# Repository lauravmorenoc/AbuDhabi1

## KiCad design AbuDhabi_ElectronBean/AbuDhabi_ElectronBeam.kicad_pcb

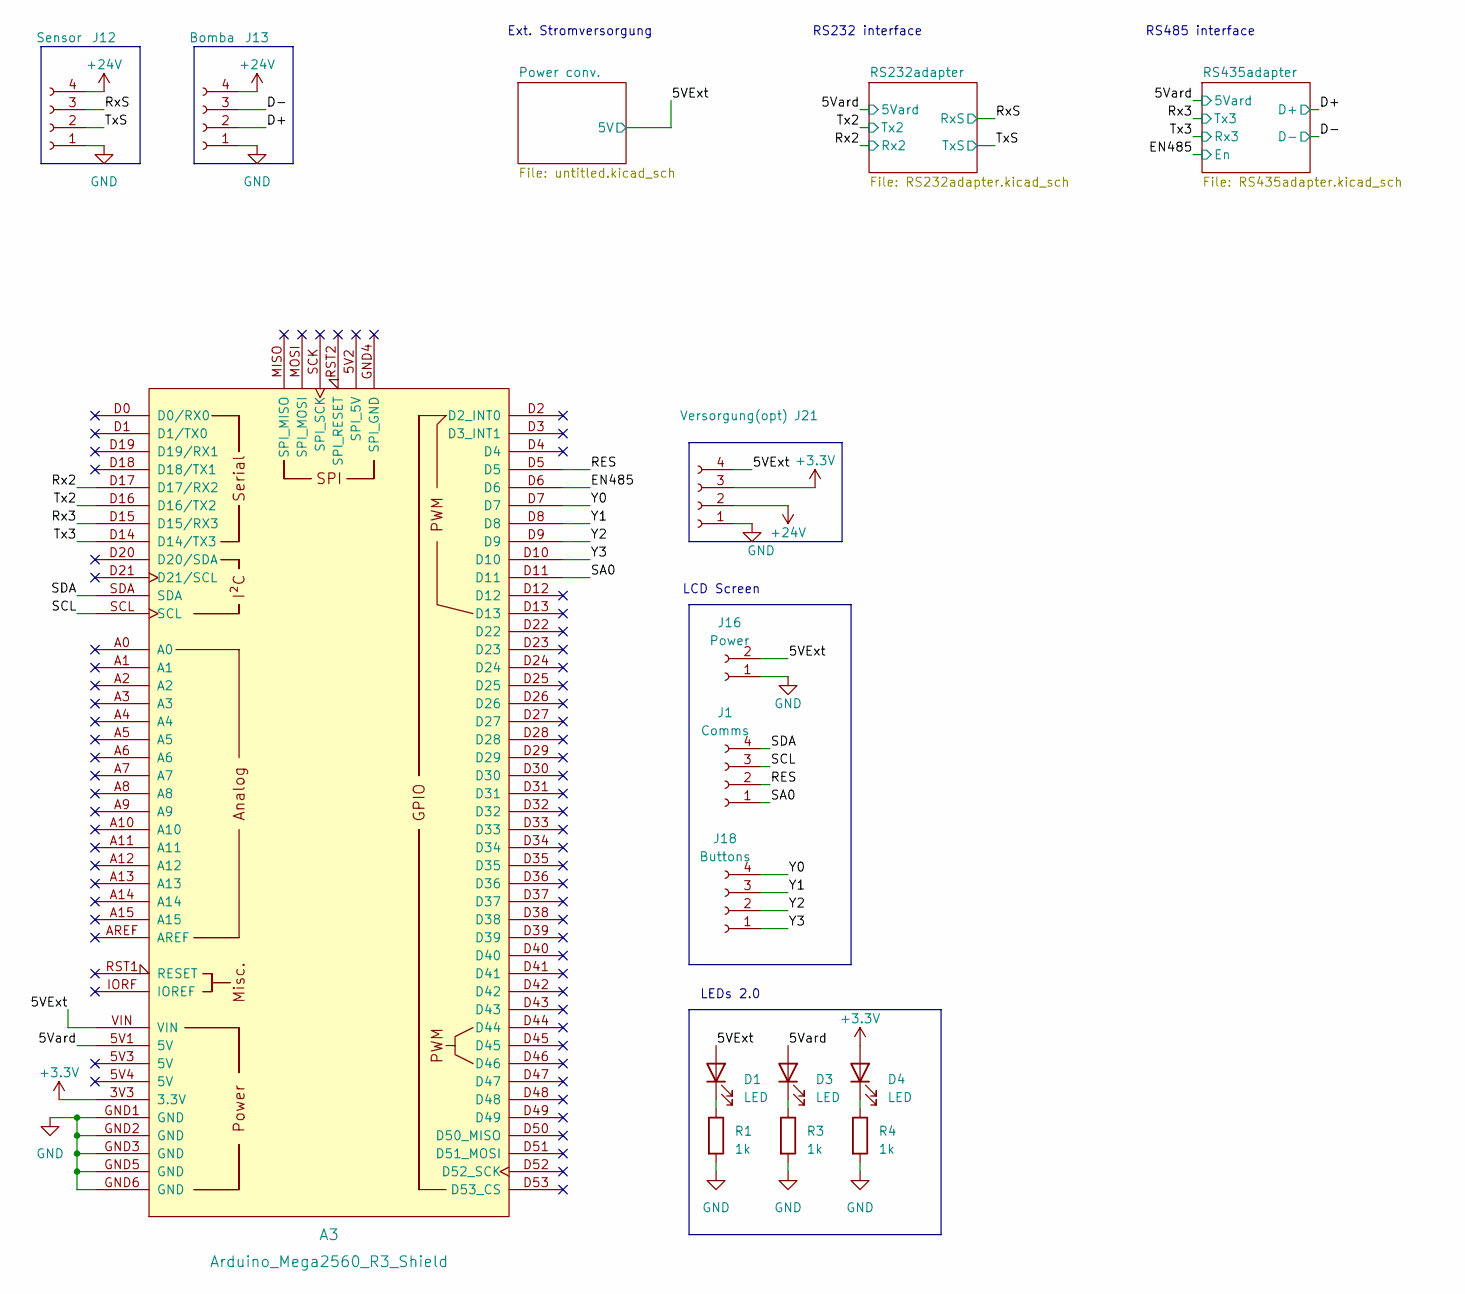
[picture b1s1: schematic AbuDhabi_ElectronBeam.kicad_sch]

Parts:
A3: Arduino_Mega2560_R3_Shield
D1, D3, D4: LED; LED_0603_1608Metric_Pad1.05x0.95mm_HandSolder
J1: Comms; PinSocket_1x04_P2.54mm_Vertical
J12: Sensor; JST_EH_B4B-EH-A_1x04_P2.50mm_Vertical
J13: Bomba; JST_EH_B4B-EH-A_1x04_P2.50mm_Vertical
J16: Power; PinSocket_1x02_P2.54mm_Vertical
J18: Buttons; PinSocket_1x04_P2.54mm_Vertical
J21: Versorgung(opt); JST_EH_B4B-EH-A_1x04_P2.50mm_Vertical
R1, R3, R4: 1k; R_0603_1608Metric_Pad0.98x0.95mm_HandSolder

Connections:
+3.3V: A3.3V3 (3.3V), D4.2 (A), J21.3
/5Vard: A3.5V1 (5V), D3.2 (A); also elsewhere on the board
/D+: J13.2; also elsewhere on the board
/D-: J13.3; also elsewhere on the board
/EN485: A3.D6; also elsewhere on the board
/RES: A3.D5, J1.2
/Rx2: A3.D17 (D17/RX2); also elsewhere on the board
/Rx3: A3.D15 (D15/RX3); also elsewhere on the board
/RxS: J12.3; also elsewhere on the board
/SA0: A3.D11, J1.1
/SCL: A3.SCL, J1.3
/SDA: A3.SDA, J1.4
/Tx2: A3.D16 (D16/TX2); also elsewhere on the board
/Tx3: A3.D14 (D14/TX3); also elsewhere on the board
/TxS: J12.2; also elsewhere on the board
/Y0: A3.D7, J18.4
/Y1: A3.D8, J18.3
/Y2: A3.D9, J18.2
/Y3: A3.D10, J18.1
GND: A3.GND1 (GND), A3.GND2 (GND), A3.GND3 (GND), A3.GND5 (GND), A3.GND6 (GND), J12.1, J13.1, J16.1, J21.1, R1.2, R3.2, R4.2; also elsewhere on the board
unnamed: D1.1 (K), R1.1
unnamed: D3.1 (K), R3.1
unnamed: D4.1 (K), R4.1

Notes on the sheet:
LCD Screen
Ext. Stromversorgung
RS485 interface
RS232 interface
LEDs 2.0

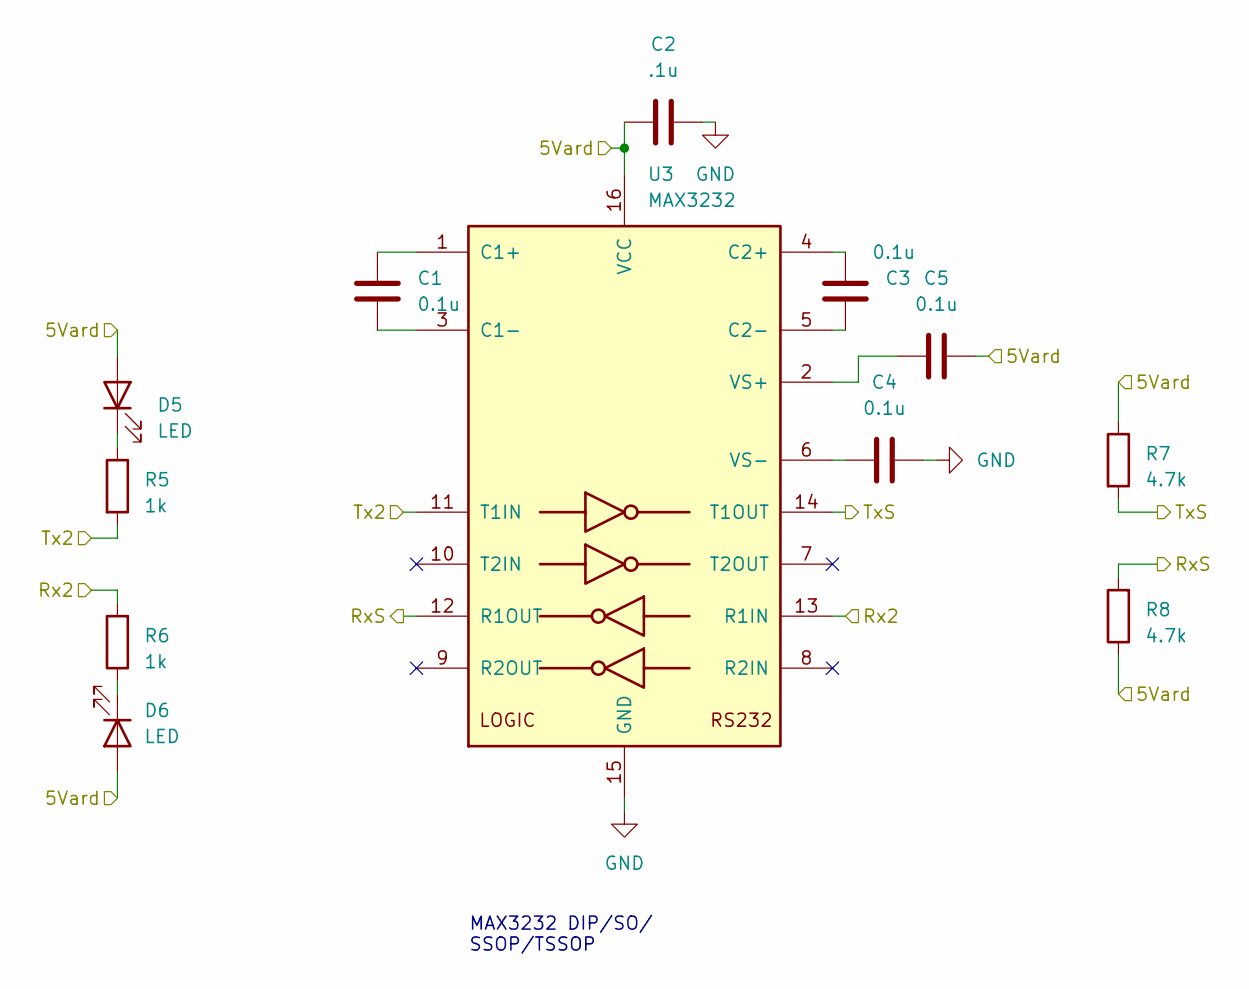
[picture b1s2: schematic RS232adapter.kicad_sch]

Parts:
C1, C3, C4, C5: 0.1u; C_0603_1608Metric
C2: .1u; C_0603_1608Metric
D5: LED; LED_0603_1608Metric
D6: LED; LED_0603_1608Metric_Pad1.05x0.95mm_HandSolder
R5, R6: 1k; R_0603_1608Metric
R7, R8: 4.7k; R_0603_1608Metric
U3: MAX3232; SOIC-16_3.9x9.9mm_P1.27mm

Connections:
/5Vard: C2.1, C5.2, D5.2 (A), D6.2 (A), R7.1, R8.1, U3.16 (VCC); also elsewhere on the board
/Rx2: R6.2, U3.13 (R1IN); also elsewhere on the board
/RxS: R8.2, U3.12 (R1OUT); also elsewhere on the board
/Tx2: R5.2, U3.11 (T1IN); also elsewhere on the board
/TxS: R7.2, U3.14 (T1OUT); also elsewhere on the board
GND: C2.2, C4.2, U3.15 (GND); also elsewhere on the board
unnamed: D5.1 (K), R5.1
unnamed: D6.1 (K), R6.1
unnamed: C1.1, U3.1 (C1+)
unnamed: C1.2, U3.3 (C1-)
unnamed: C3.1, U3.4 (C2+)
unnamed: C3.2, U3.5 (C2-)
unnamed: C5.1, U3.2 (VS+)
unnamed: C4.1, U3.6 (VS-)

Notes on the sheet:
MAX3232 DIP/SO/ SSOP/TSSOP

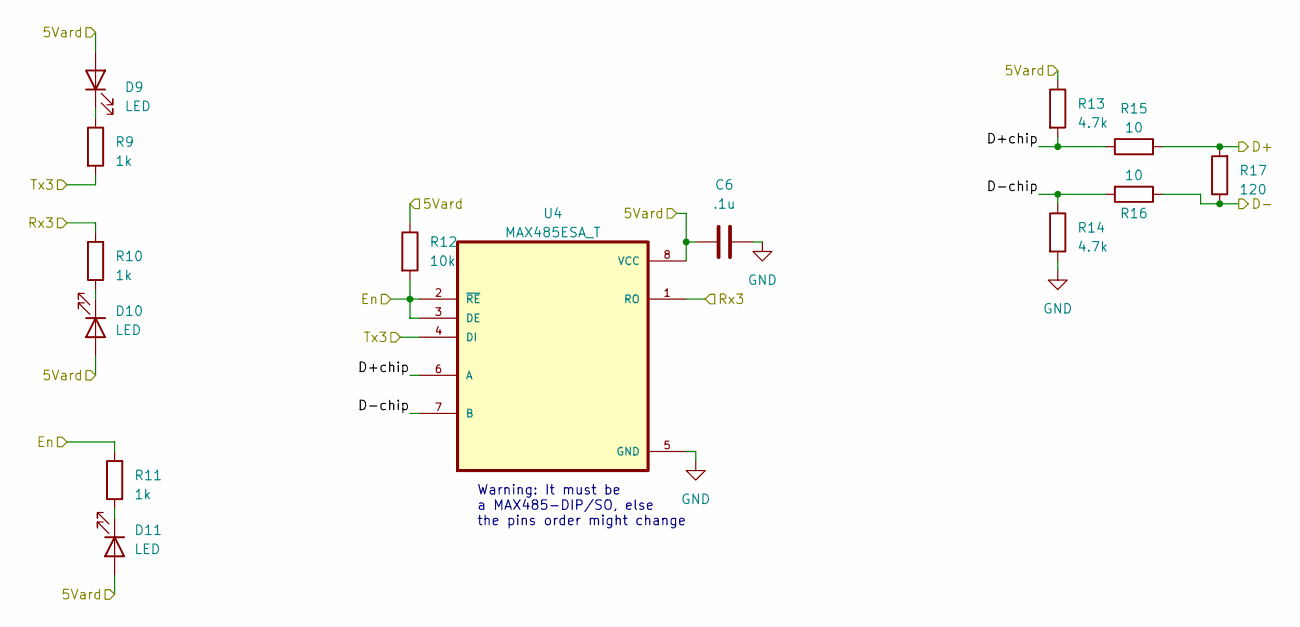
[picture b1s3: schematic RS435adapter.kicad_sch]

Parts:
C6: .1u; C_0603_1608Metric
D9, D10, D11: LED; LED_0603_1608Metric
R9, R10, R11: 1k; R_0603_1608Metric
R12: 10k; R_0603_1608Metric
R13, R14: 4.7k; R_0603_1608Metric
R15, R16: 10; R_0603_1608Metric
R17: 120; R_0603_1608Metric
U4: MAX485ESA_T; SOIC127P600X175-8N

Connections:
/5Vard: C6.1, D9.2 (A), D10.2 (A), D11.2 (A), R12.1, R13.1, U4.8 (VCC); also elsewhere on the board
/D+: R15.2, R17.2; also elsewhere on the board
/D-: R16.1, R17.1; also elsewhere on the board
/EN485: R11.2, R12.2, U4.2 (~RE), U4.3 (DE); also elsewhere on the board
/RS435adapter/D+chip: R13.2, R15.1, U4.6 (A)
/RS435adapter/D-chip: R14.1, R16.2, U4.7 (B)
/Rx3: R9.2, U4.4 (DI); also elsewhere on the board
/Tx3: R10.2, U4.1 (RO); also elsewhere on the board
GND: C6.2, R14.2, U4.5 (GND); also elsewhere on the board
unnamed: D9.1 (K), R9.1
unnamed: D10.1 (K), R10.1
unnamed: D11.1 (K), R11.1

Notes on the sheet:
Warning: It must be a MAX485-DIP/SO, else the pins order might change

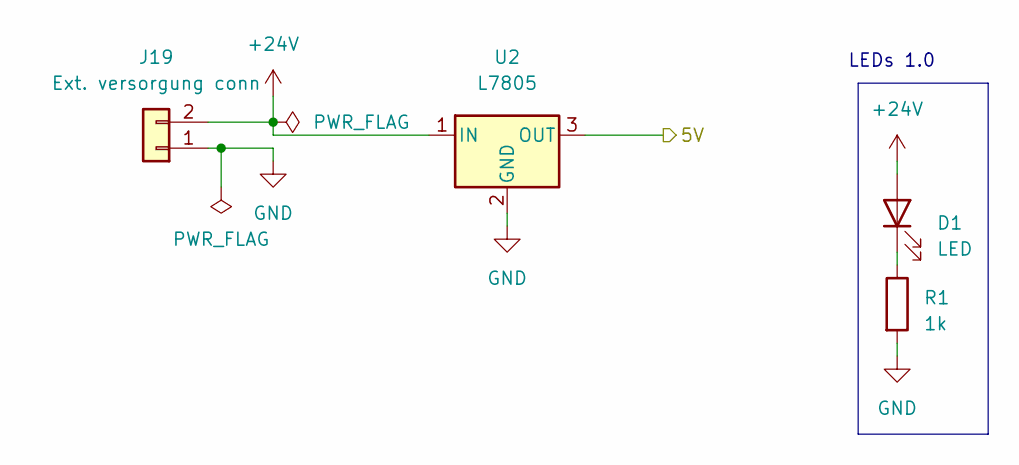
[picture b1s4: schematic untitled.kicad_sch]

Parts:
D1: LED; LED_0603_1608Metric_Pad1.05x0.95mm_HandSolder
J19: Ext. versorgung conn; JST_EH_B2B-EH-A_1x02_P2.50mm_Vertical
R1: 1k; R_0603_1608Metric
U2: L7805; TO-220-3_Vertical

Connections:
GND: J19.1, R1.2, U2.2 (GND); also elsewhere on the board
unnamed: D1.1 (K), R1.1

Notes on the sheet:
LEDs 1.0

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
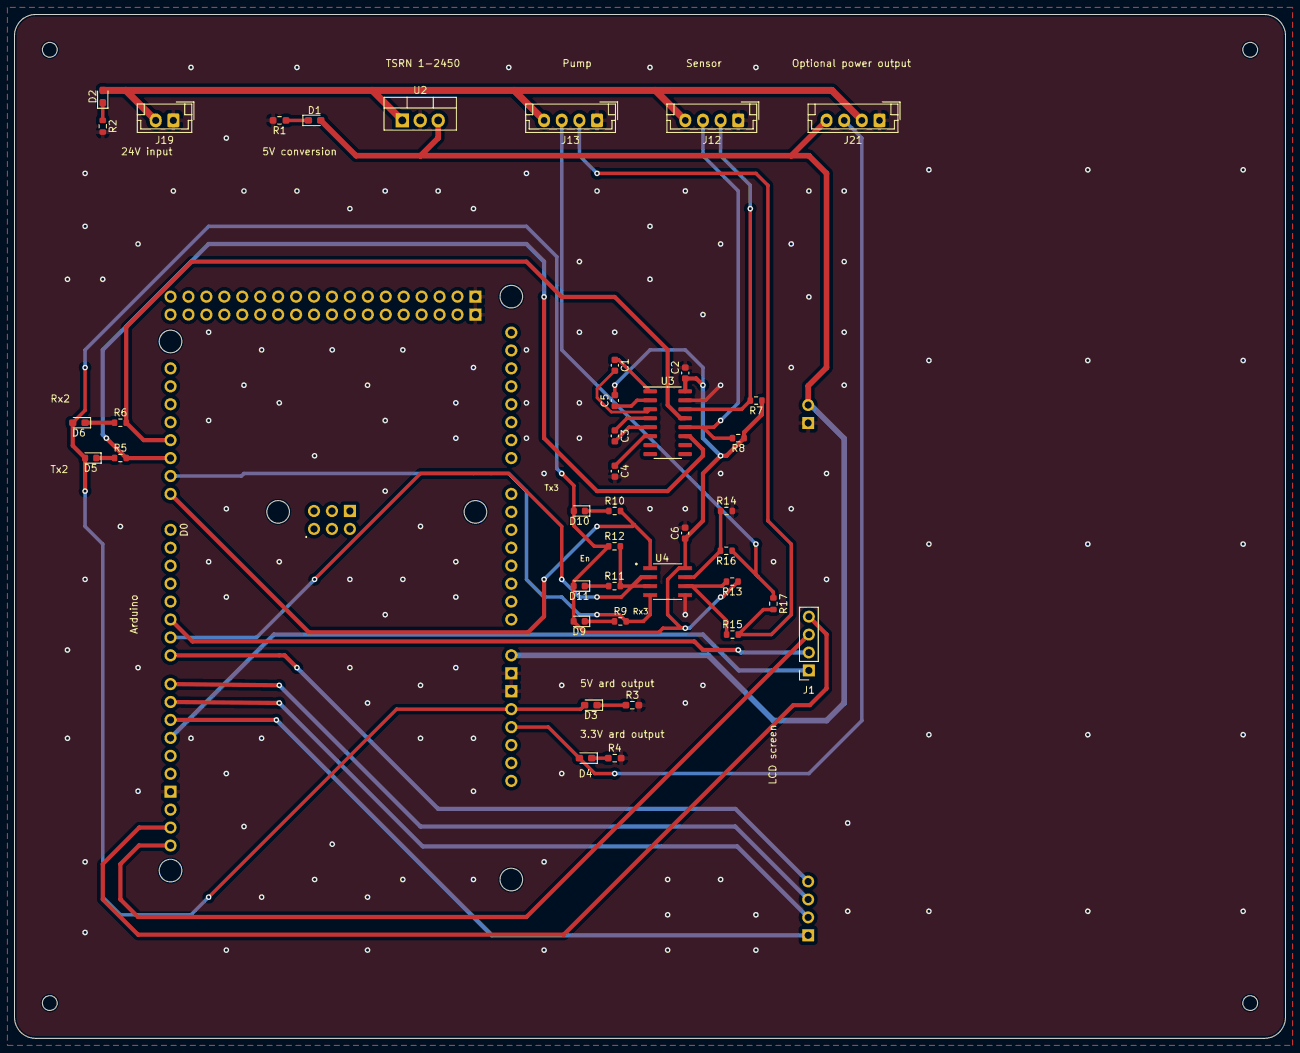
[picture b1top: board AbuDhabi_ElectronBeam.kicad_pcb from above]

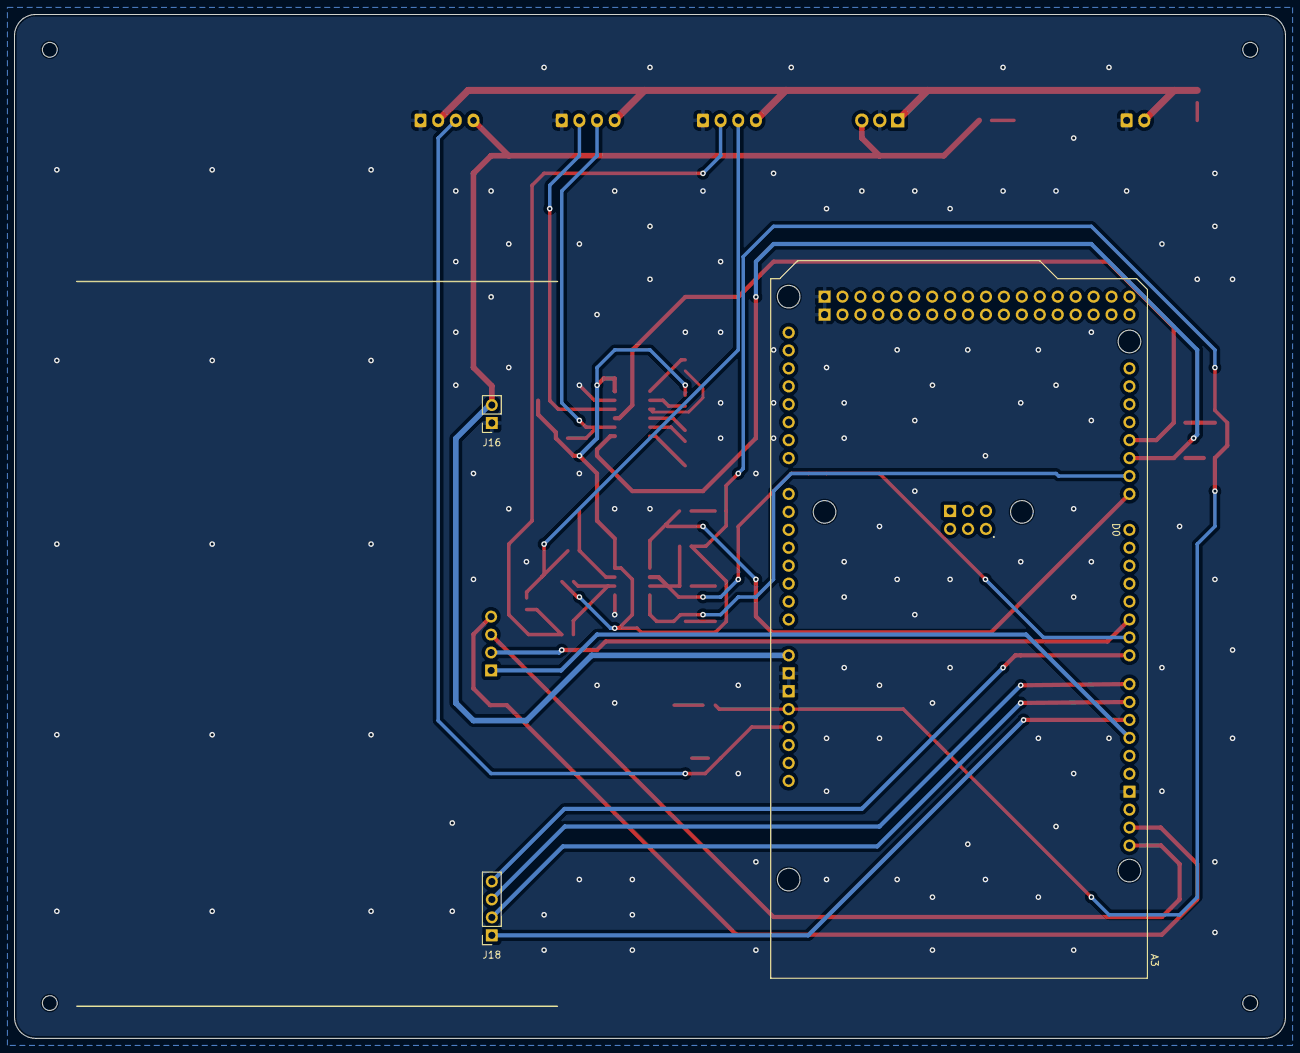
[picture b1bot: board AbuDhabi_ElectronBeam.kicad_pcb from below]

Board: 2 copper layers, 180.0 x 145.0 mm, 43 parts (2 on the bottom side), 39 nets.

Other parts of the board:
D2: LED; LED_0603_1608Metric_Pad1.05x0.95mm_HandSolder
R2: 1k; R_0603_1608Metric

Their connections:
GND: R2.2; also elsewhere on the board
unnamed: D2.1 (K), R2.1

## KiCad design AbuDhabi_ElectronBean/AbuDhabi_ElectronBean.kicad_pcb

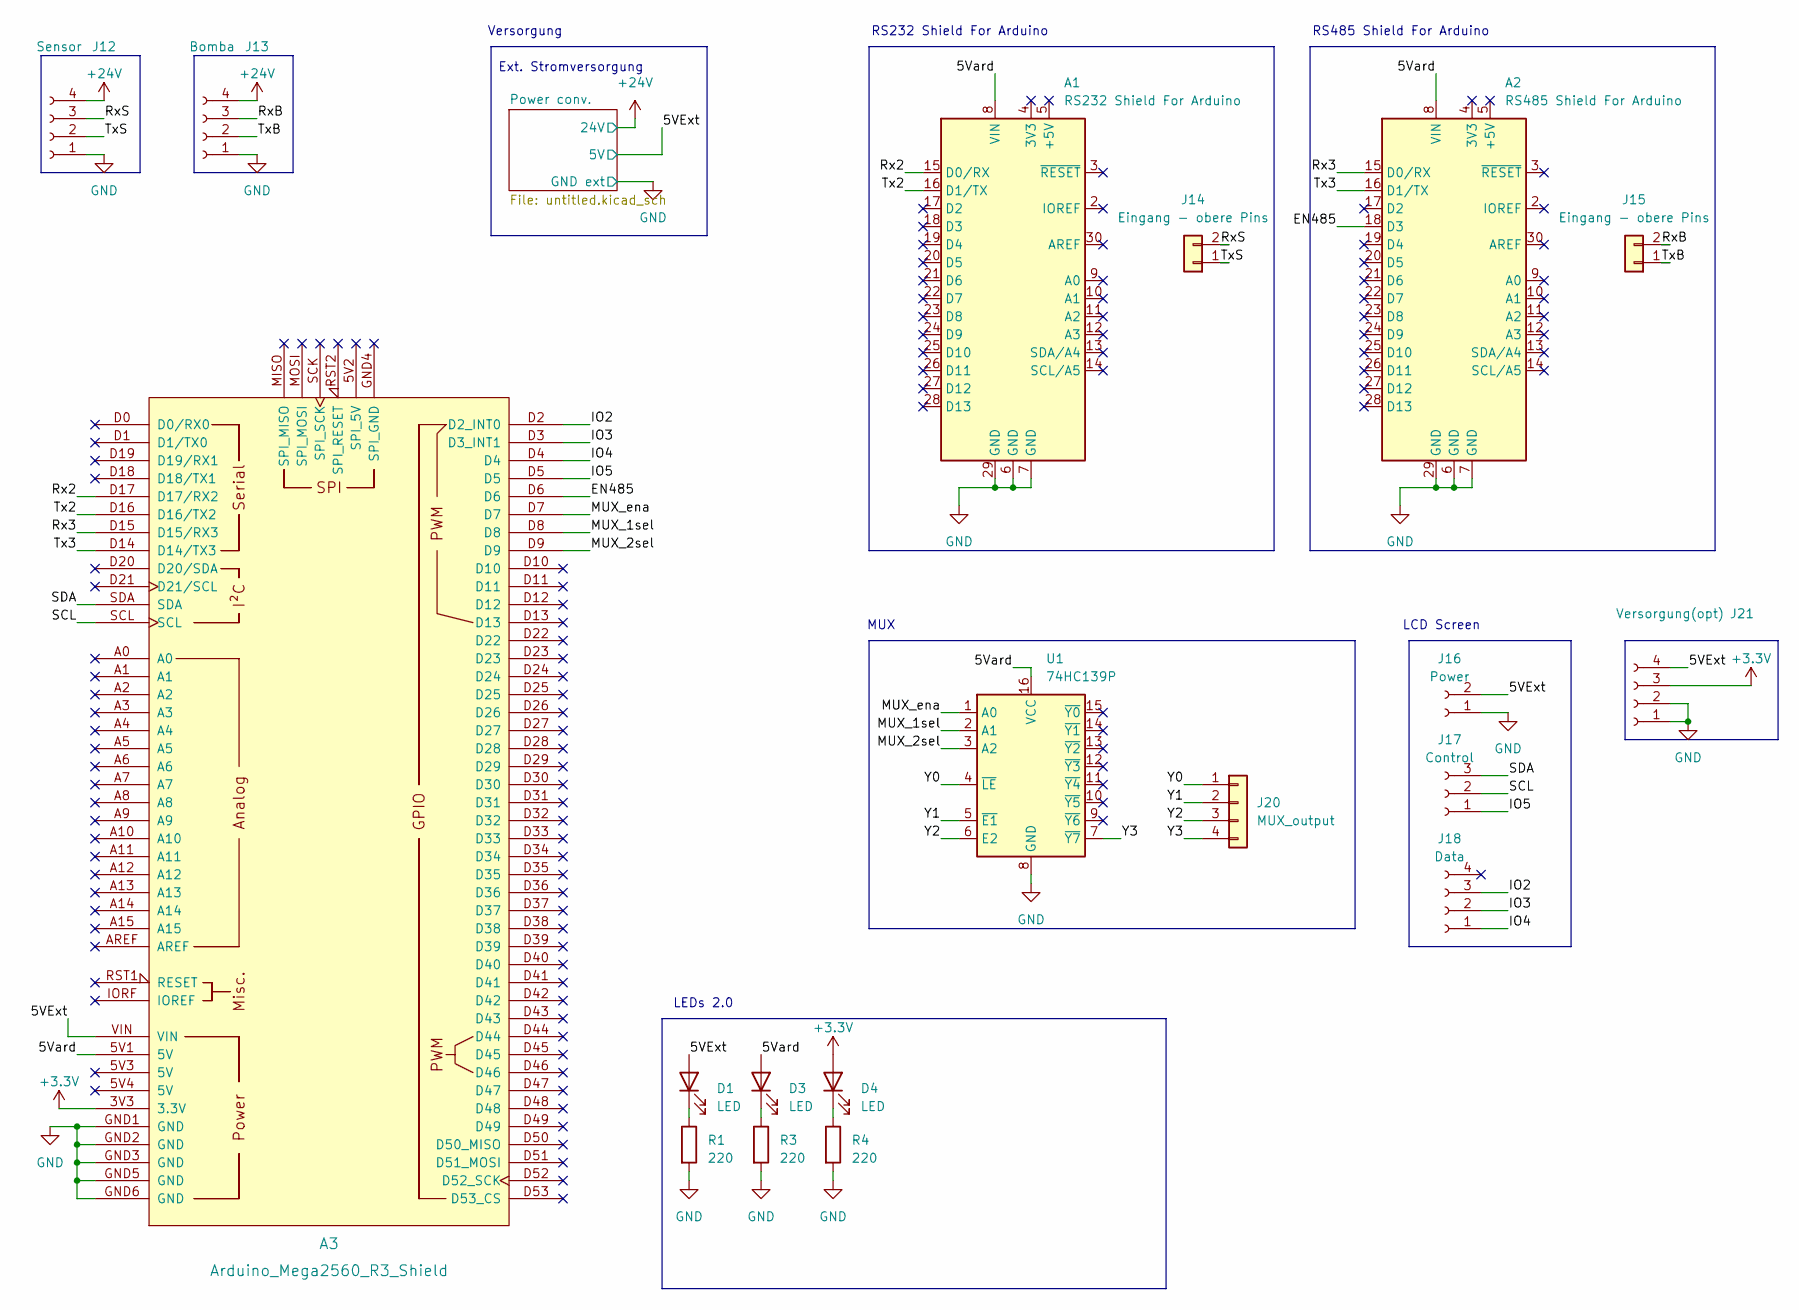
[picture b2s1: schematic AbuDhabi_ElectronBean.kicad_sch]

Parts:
A1: RS232 Shield For Arduino; Arduino_UNO_R2
A2: RS485 Shield For Arduino; Arduino_UNO_R2
A3: Arduino_Mega2560_R3_Shield
D1, D3, D4: LED; LED_0603_1608Metric_Pad1.05x0.95mm_HandSolder
J12: Sensor; JST_EH_B4B-EH-A_1x04_P2.50mm_Vertical
J13: Bomba; JST_EH_B4B-EH-A_1x04_P2.50mm_Vertical
J14, J15: Eingang - obere Pins; JST_EH_B2B-EH-A_1x02_P2.50mm_Vertical
J16: Power; PinSocket_1x02_P2.54mm_Vertical
J17: Control; PinSocket_1x03_P2.54mm_Vertical
J18: Data; PinSocket_1x04_P2.54mm_Vertical
J20: MUX_output; JST_EH_B4B-EH-A_1x04_P2.50mm_Vertical
J21: Versorgung(opt); JST_EH_B4B-EH-A_1x04_P2.50mm_Vertical
R1, R3, R4: 220; R_0805_2012Metric_Pad1.20x1.40mm_HandSolder
U1: 74HC139P; DIP-16_W7.62mm

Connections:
+3.3V: A3.3V3 (3.3V), D4.2 (A), J21.3
/5Vard: A1.8 (VIN), A2.8 (VIN), A3.5V1 (5V), D3.2 (A), U1.16 (VCC)
/EN485: A2.18 (D3), A3.D6
/IO2: A3.D2 (D2_INT0), J18.3
/IO3: A3.D3 (D3_INT1), J18.2
/IO4: A3.D4, J18.1
/IO5: A3.D5, J17.1
/MUX_1sel: A3.D8, U1.2 (A1)
/MUX_2sel: A3.D9, U1.3 (A2)
/MUX_ena: A3.D7, U1.1 (A0)
/Rx2: A1.15 (D0/RX), A3.D17 (D17/RX2)
/Rx3: A2.15 (D0/RX), A3.D15 (D15/RX3)
/RxB: J13.3, J15.2
/RxS: J12.3, J14.2
/SCL: A3.SCL, J17.2
/SDA: A3.SDA, J17.3
/Tx2: A1.16 (D1/TX), A3.D16 (D16/TX2)
/Tx3: A2.16 (D1/TX), A3.D14 (D14/TX3)
/TxB: J13.2, J15.1
/TxS: J12.2, J14.1
/Y0: J20.1, U1.4 (~LE)
/Y1: J20.2, U1.5 (~E1)
/Y2: J20.3, U1.6 (E2)
/Y3: J20.4, U1.7 (~Y7)
GND: A1.6 (GND), A1.7 (GND), A1.29 (GND), A2.6 (GND), A2.7 (GND), A2.29 (GND), A3.GND1 (GND), A3.GND2 (GND), A3.GND3 (GND), A3.GND5 (GND), A3.GND6 (GND), J12.1, J13.1, J16.1, J21.1, J21.2, R1.2, R3.2, R4.2, U1.8 (GND); also elsewhere on the board
unnamed: D1.1 (K), R1.1
unnamed: D3.1 (K), R3.1
unnamed: D4.1 (K), R4.1

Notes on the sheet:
RS232 Shield For Arduino
Versorgung
LCD Screen
Ext. Stromversorgung
RS485 Shield For Arduino
MUX
LEDs 2.0

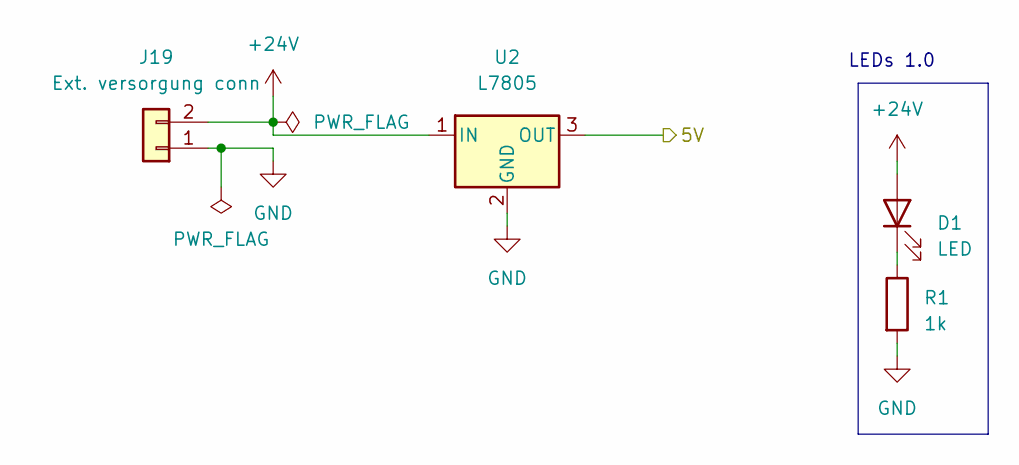
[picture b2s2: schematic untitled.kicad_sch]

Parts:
D1: LED; LED_0603_1608Metric_Pad1.05x0.95mm_HandSolder
J19: Ext. versorgung conn; JST_EH_B2B-EH-A_1x02_P2.50mm_Vertical
R1: 1k; R_0603_1608Metric
U2: L7805; TO-220-3_Vertical

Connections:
GND: J19.1, R1.2, U2.2 (GND); also elsewhere on the board
unnamed: D1.1 (K), R1.1

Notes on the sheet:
LEDs 1.0

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
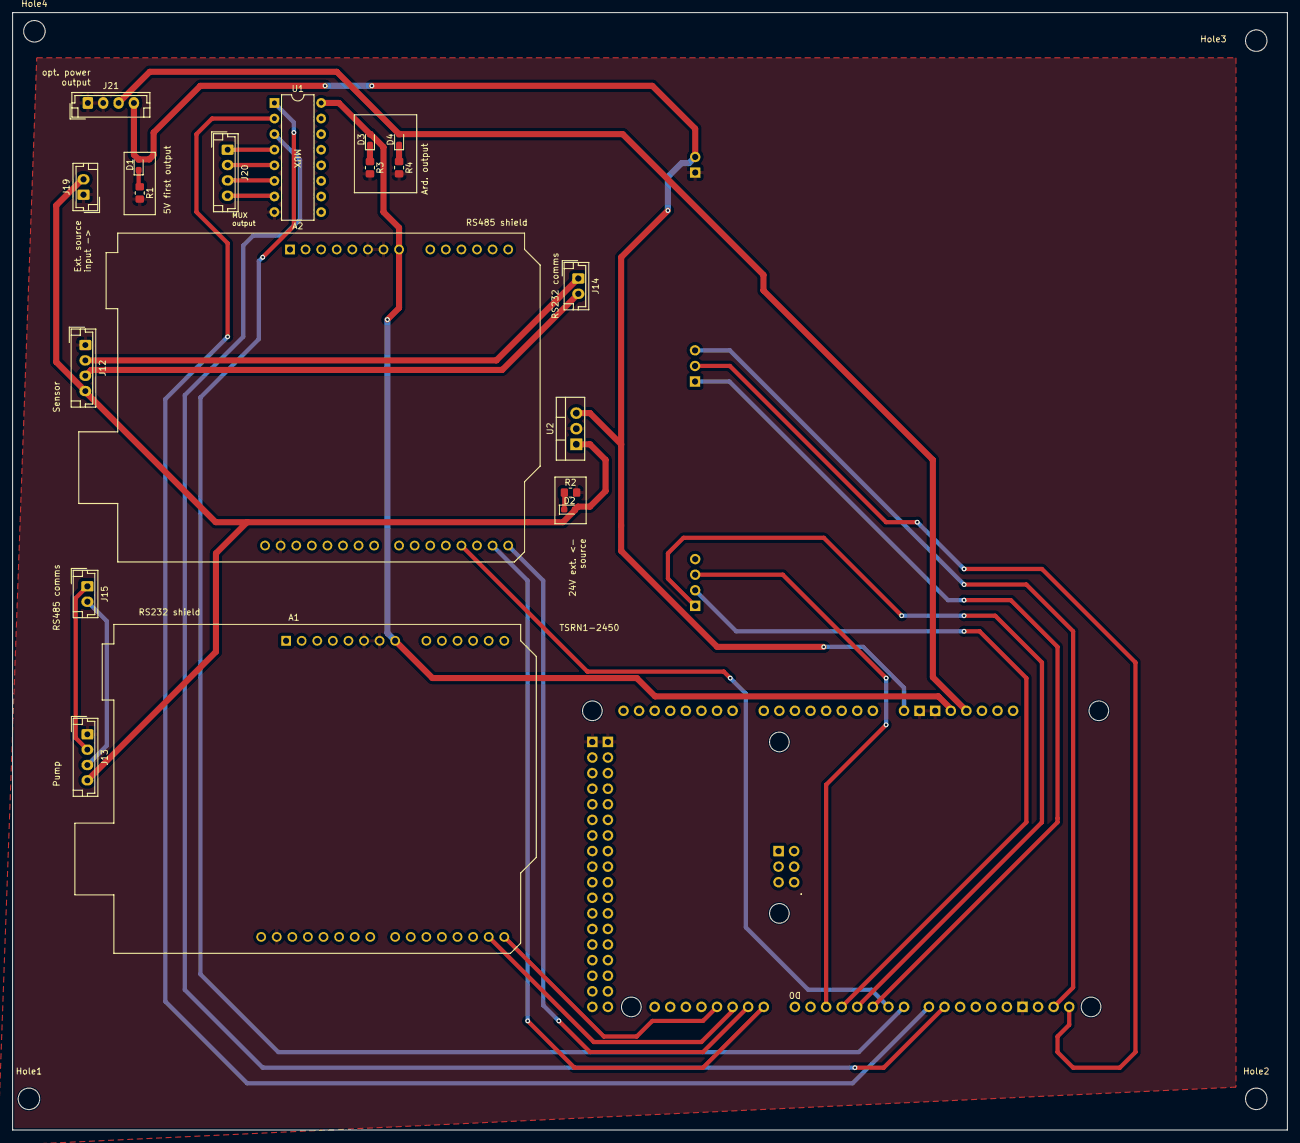
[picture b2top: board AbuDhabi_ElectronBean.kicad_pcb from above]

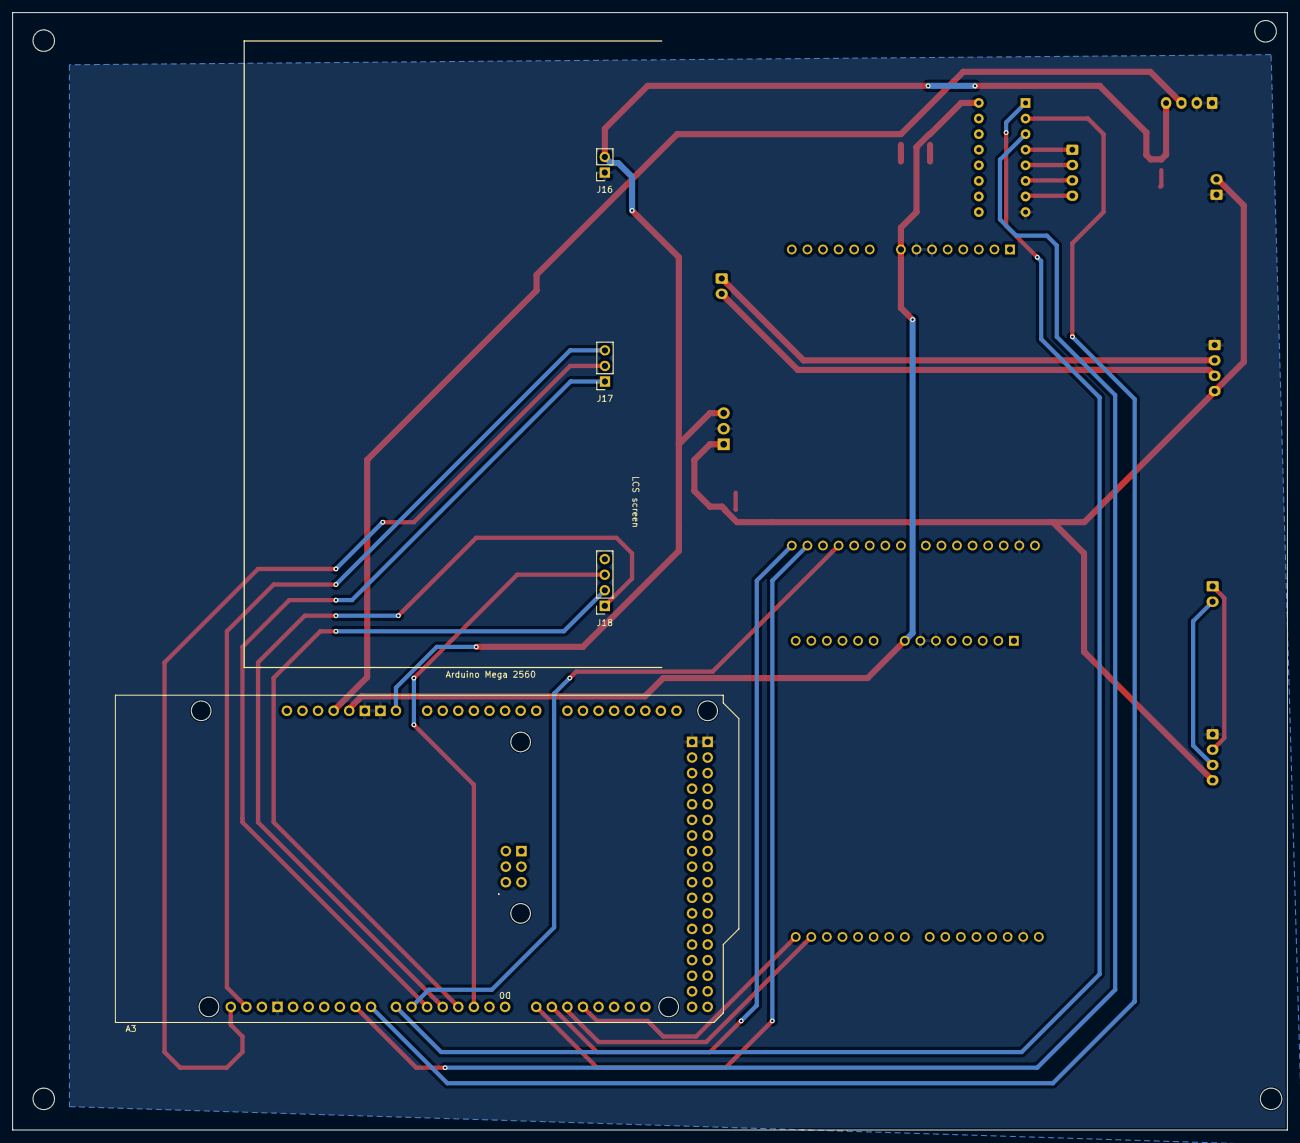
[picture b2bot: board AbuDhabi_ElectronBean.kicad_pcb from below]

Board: 2 copper layers, 207.8 x 182.1 mm, 27 parts (3 on the bottom side), 31 nets.

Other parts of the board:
D2: LED; LED_0603_1608Metric_Pad1.05x0.95mm_HandSolder
Hole1, Hole2, Hole3, Hole4: MountingHole_3.5mm
R2: 220; R_0805_2012Metric_Pad1.20x1.40mm_HandSolder

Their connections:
GND: R2.2; also elsewhere on the board
unnamed: D2.1 (K), R2.1

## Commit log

2023-09-19 First upload PCB
2023-09-19 Arduino Mega 2560 symbol and footprint adition
2023-09-19 Arduino Mega footpring change and LEDs addition
2023-09-25 A bit of order
2023-09-25 Nothing
2023-09-25 Routing part 1
2023-09-26 Everything routed and DRC checked and corrected, ready to print
2023-09-26 LCD screen update
2023-09-28 I2c address scanner code added
2023-10-09 LCD PCB Components mirror
2023-10-09 LCD PCB final touches
2023-10-16 RS232 und RS435 shields entfernt
2023-10-16 RS435 interface start
2023-10-18 RS232 interface changes (completed) and RS485 interface in working...
2023-10-20 LCD PCB changes according to Robins suggestions. Still pending one thing
2023-10-23 Just reading bout RS485
2023-10-24 Finally understood RS485
2023-10-25 LCD PCB finished (again)
2023-10-25 Some changes on the full PCB (Robin's folder). Ready to trace.
    All changes are being made (from now onwards) in Robins' folder (so it also keeps his changes).
2023-11-20 Main board file updated. Added Arduino code for the LCD
    The LCD is not working yet though.
2024-01-03 Merging branches
